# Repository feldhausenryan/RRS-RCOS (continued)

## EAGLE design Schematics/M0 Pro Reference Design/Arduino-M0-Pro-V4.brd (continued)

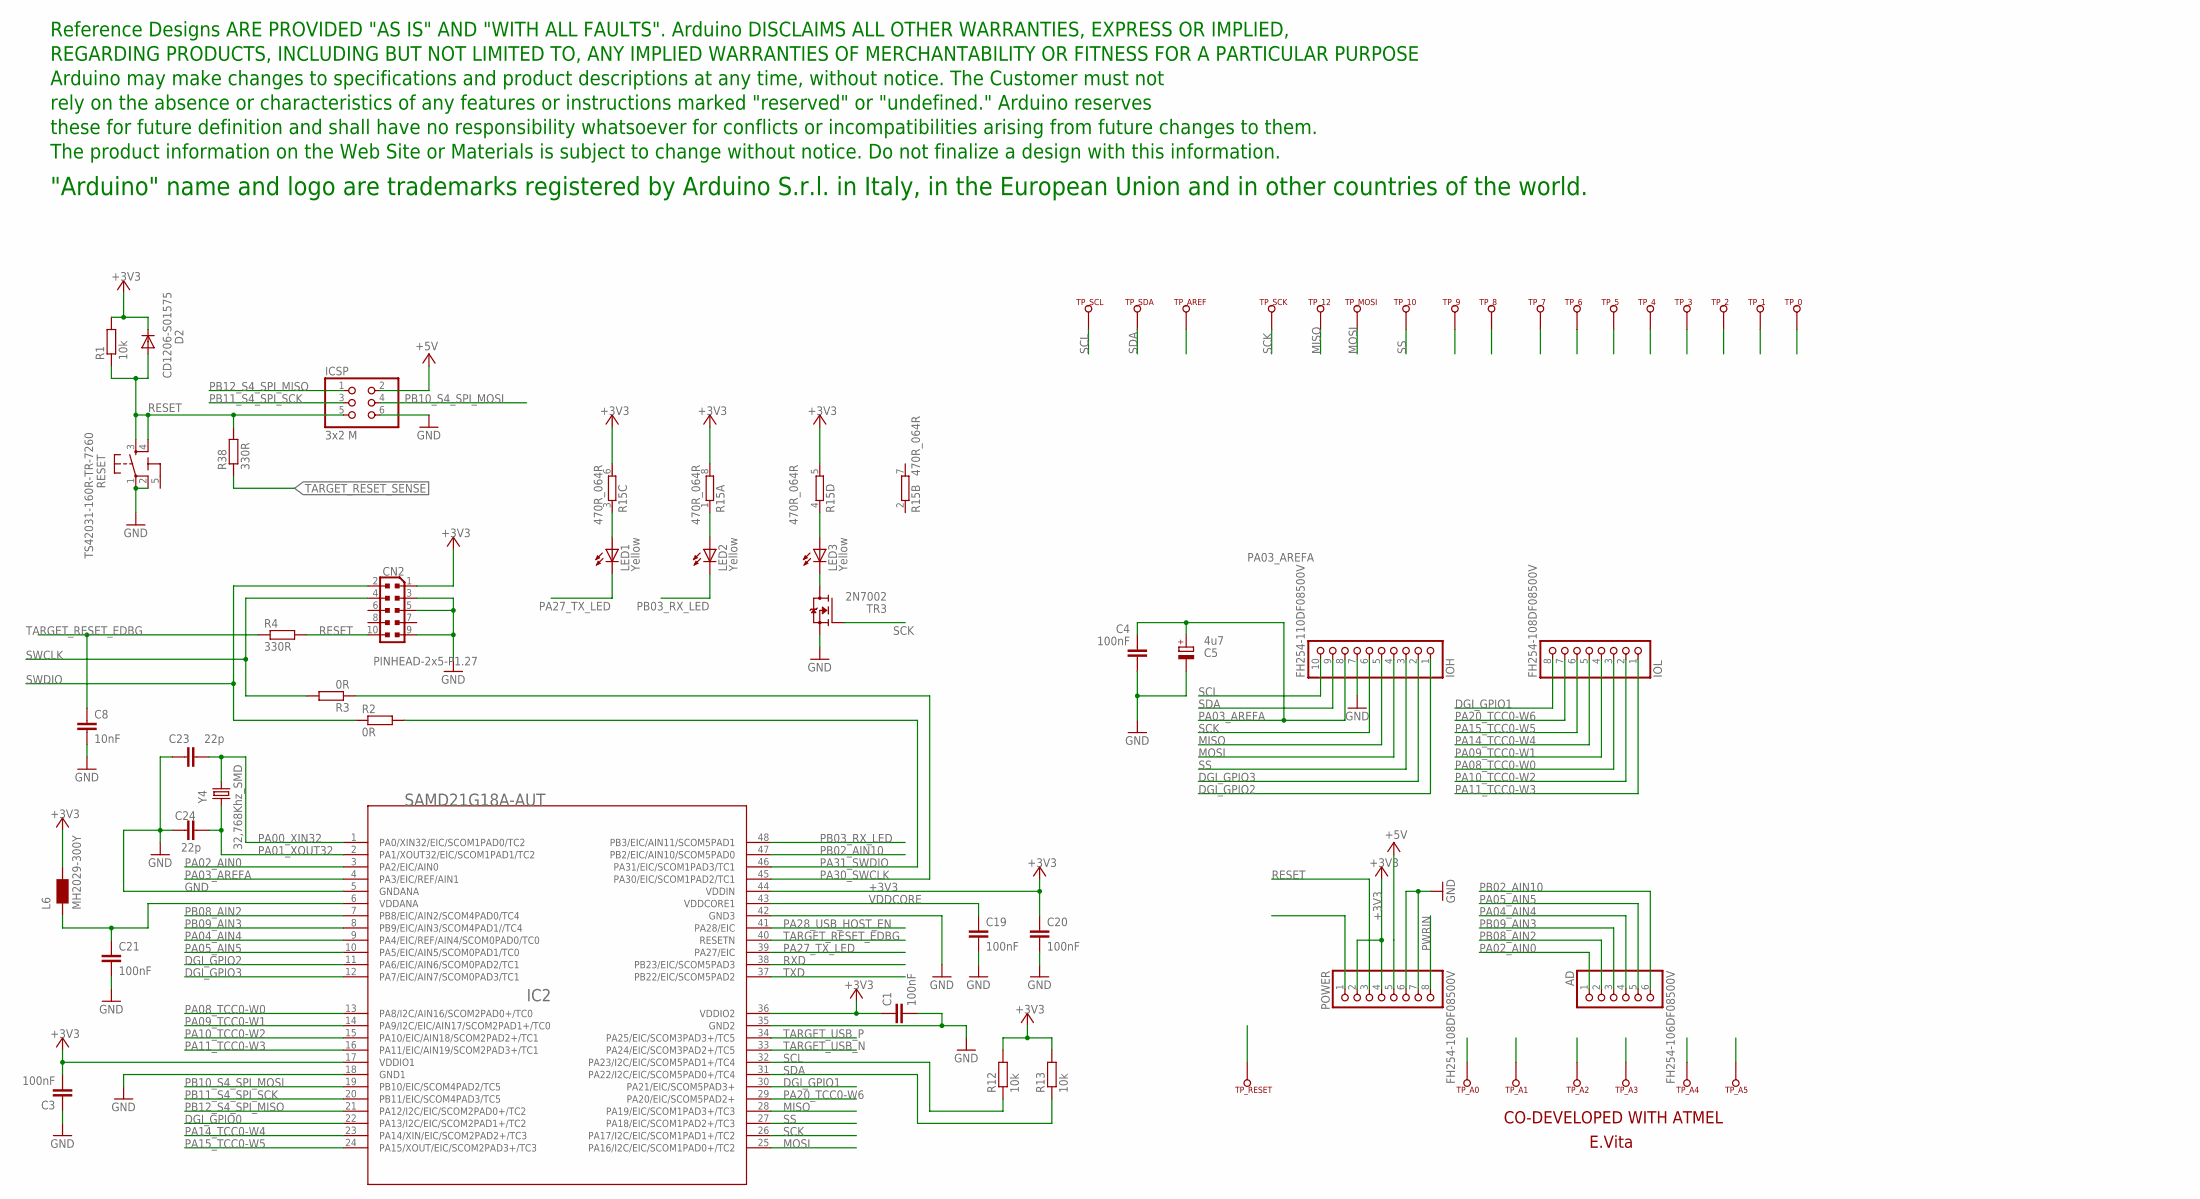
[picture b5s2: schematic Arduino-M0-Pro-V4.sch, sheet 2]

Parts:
AD: FH254-106DF08500V; 1X06
C1, C3, C4, C19, C20, C21: 100nF; C0603-ROUND
C5: 4u7; SMC_A
C8: 10nF; C0603-ROUND
C23, C24: 22p; C0603-ROUND
CN2: PINHEAD-2x5-P1.27; PINHEAD_2X05_127
D2: CD1206-S01575; MINIMELF
IC2: SAMD21G18A-AUT; TQFP48-7X7
ICSP: 3x2 M; 2X03
IOH: FH254-110DF08500V; 1X10
IOL: FH254-108DF08500V; 1X08
L6: MH2029-300Y; 0805
LED1, LED2, LED3: Yellow; CHIPLED_0805
POWER: FH254-108DF08500V; 1X08
R1, R12, R13: 10k; R0603-ROUND
R2, R3: 0R; R0603-ROUND
R4, R38: 330R; R0603-ROUND
R15: 470R_064R; CAY16
RESET: TS42031-160R-TR-7260; TS42
TP_0, TP_1, TP_2, TP_3, TP_4, TP_5, TP_6, TP_7, TP_8, TP_9, TP_10, TP_12: TP_SP; TP-SP
TP_A0, TP_A1, TP_A2, TP_A3, TP_A4, TP_A5: TP_SP; TP-SP
TP_AREF: TP_SP; TP-SP
TP_MOSI: TP_SP; TP-SP
TP_RESET: TP_SP; TP-SP
TP_SCK: TP_SP; TP-SP
TP_SCL: TP_SP; TP-SP
TP_SDA: TP_SP; TP-SP
TR3: 2N7002; SOT-23
U$2: DISCLAIMER
Y4: 32,768Khz_SMD; RESONATOR_EPSON_FC_145

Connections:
5-GND: RESET.5 (5-GND)
+3V3: C1.1, C3.2, C20.1, CN2.1, D2.C, IC2.17 (VDDIO1), IC2.36 (VDDIO2), IC2.44 (VDDIN), L6.2, POWER.2, POWER.4, R1.2, R12.2, R13.2, R15.5 (2), R15.6 (2), R15.8 (2); also elsewhere on the board
+5V: ICSP.2, POWER.5; also elsewhere on the board
DGI_GPIO0: IC2.22 (PA13/I2C/EIC/SCOM2PAD1+/TC2); also elsewhere on the board
DGI_GPIO1: IC2.30 (PA21/EIC/SCOM5PAD3+), IOL.8, TP_7.X; also elsewhere on the board
DGI_GPIO2: IC2.11 (PA6/EIC/AIN6/SCOM0PAD2/TC1), IOH.1, TP_8.X; also elsewhere on the board
DGI_GPIO3: IC2.12 (PA7/EIC/AIN7/SCOM0PAD3/TC1), IOH.2, TP_9.X; also elsewhere on the board
GND: C1.2, C3.1, C4.2, C5.-, C8.2, C19.2, C20.2, C21.2, C23.1, C24.1, CN2.3, CN2.5, CN2.9, IC2.5 (GNDANA), IC2.18 (GND1), IC2.35 (GND2), IC2.42 (GND3), ICSP.6, IOH.7, POWER.6, POWER.7, RESET.1, RESET.2, TR3.2 (S); also elsewhere on the board
MISO: IC2.28 (PA19/EIC/SCOM1PAD3+/TC3), IOH.5, TP_12.X; also elsewhere on the board
MOSI: IC2.25 (PA16/I2C/EIC/SCOM1PAD0+/TC2), IOH.4, TP_MOSI.X; also elsewhere on the board
unnamed: LED3.C, TR3.1 (D)
unnamed: C21.1, IC2.6 (VDDANA), L6.1
unnamed: LED1.A, R15.3 (1)
unnamed: LED2.A, R15.1
unnamed: LED3.A, R15.4 (1)
PA00_XIN32: C23.2, IC2.1 (PA0/XIN32/EIC/SCOM1PAD0/TC2), Y4.P$2 (2)
PA01_XOUT32: C24.2, IC2.2 (PA1/XOUT32/EIC/SCOM1PAD1/TC2), Y4.P$1 (1)
PA02_AIN0: AD.1, IC2.3 (PA2/EIC/AIN0), TP_A0.X
PA03_AREFA: C4.1, C5.+, IC2.4 (PA3/EIC/REF/AIN1), IOH.8, TP_AREF.X
PA04_AIN4: AD.4, IC2.9 (PA4/EIC/REF/AIN4/SCOM0PAD0/TC0), TP_A3.X
PA05_AIN5: AD.5, IC2.10 (PA5/EIC/AIN5/SCOM0PAD1/TC0), TP_A4.X
PA08_TCC0-W0: IC2.13 (PA8/I2C/AIN16/SCOM2PAD0+/TC0), IOL.3, TP_2.X
PA09_TCC0-W1: IC2.14 (PA9/I2C/EIC/AIN17/SCOM2PAD1+/TC0), IOL.4, TP_3.X
PA10_TCC0-W2: IC2.15 (PA10/EIC/AIN18/SCOM2PAD2+/TC1), IOL.2, TP_1.X
PA11_TCC0-W3: IC2.16 (PA11/EIC/AIN19/SCOM2PAD3+/TC1), IOL.1, TP_0.X
PA14_TCC0-W4: IC2.23 (PA14/XIN/EIC/SCOM2PAD2+/TC3), IOL.5, TP_4.X
PA15_TCC0-W5: IC2.24 (PA15/XOUT/EIC/SCOM2PAD3+/TC3), IOL.6, TP_5.X
PA20_TCC0-W6: IC2.29 (PA20/EIC/SCOM5PAD2+), IOL.7, TP_6.X
PA27_TX_LED: IC2.39 (PA27/EIC), LED1.C
PA28_USB_HOST_EN: IC2.41 (PA28/EIC); also elsewhere on the board
PA30_SWCLK: IC2.45 (PA30/EIC/SCOM1PAD2/TC1), R3.1
PA31_SWDIO: IC2.46 (PA31/EIC/SCOM1PAD3/TC1), R2.2
PB02_AIN10: AD.6, IC2.47 (PB2/EIC/AIN10/SCOM5PAD0), TP_A5.X
PB03_RX_LED: IC2.48 (PB3/EIC/AIN11/SCOM5PAD1), LED2.C
PB08_AIN2: AD.2, IC2.7 (PB8/EIC/AIN2/SCOM4PAD0/TC4), TP_A1.X
PB09_AIN3: AD.3, IC2.8 (PB9/EIC/AIN3/SCOM4PAD1//TC4), TP_A2.X
PB10_S4_SPI_MOSI: IC2.19 (PB10/EIC/SCOM4PAD2/TC5), ICSP.4
PB11_S4_SPI_SCK: IC2.20 (PB11/EIC/SCOM4PAD3/TC5), ICSP.3
PB12_S4_SPI_MISO: IC2.21 (PA12/I2C/EIC/SCOM2PAD0+/TC2), ICSP.1
PWRIN: POWER.8; also elsewhere on the board
RESET: CN2.10, D2.A, ICSP.5, POWER.3, R1.1, R4.2, R38.2, RESET.3, RESET.4, TP_RESET.X
RXD: IC2.38 (PB23/EIC/SCOM5PAD3); also elsewhere on the board
SCK: IC2.26 (PA17/I2C/EIC/SCOM1PAD1+/TC2), IOH.6, TP_SCK.X, TR3.3 (G); also elsewhere on the board
SCL: IC2.32 (PA23/I2C/EIC/SCOM5PAD1+/TC4), IOH.10, R12.1, TP_SCL.X; also elsewhere on the board
SDA: IC2.31 (PA22/I2C/EIC/SCOM5PAD0+/TC4), IOH.9, R13.1, TP_SDA.X; also elsewhere on the board
SS: IC2.27 (PA18/EIC/SCOM1PAD2+/TC3), IOH.3, TP_10.X; also elsewhere on the board
SWCLK: CN2.4, R3.2; also elsewhere on the board
SWDIO: CN2.2, R2.1; also elsewhere on the board
TARGET_RESET_EDBG: C8.1, IC2.40 (RESETN), R4.1; also elsewhere on the board
TARGET_RESET_SENSE: R38.1; also elsewhere on the board
TARGET_USB_N: IC2.33 (PA24/EIC/SCOM3PAD2+/TC5); also elsewhere on the board
TARGET_USB_P: IC2.34 (PA25/EIC/SCOM3PAD3+/TC5); also elsewhere on the board
TXD: IC2.37 (PB22/EIC/SCOM5PAD2); also elsewhere on the board
VDDCORE: C19.1, IC2.43 (VDDCORE1)

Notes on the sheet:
CO-DEVELOPED WITH ATMEL
E.Vita

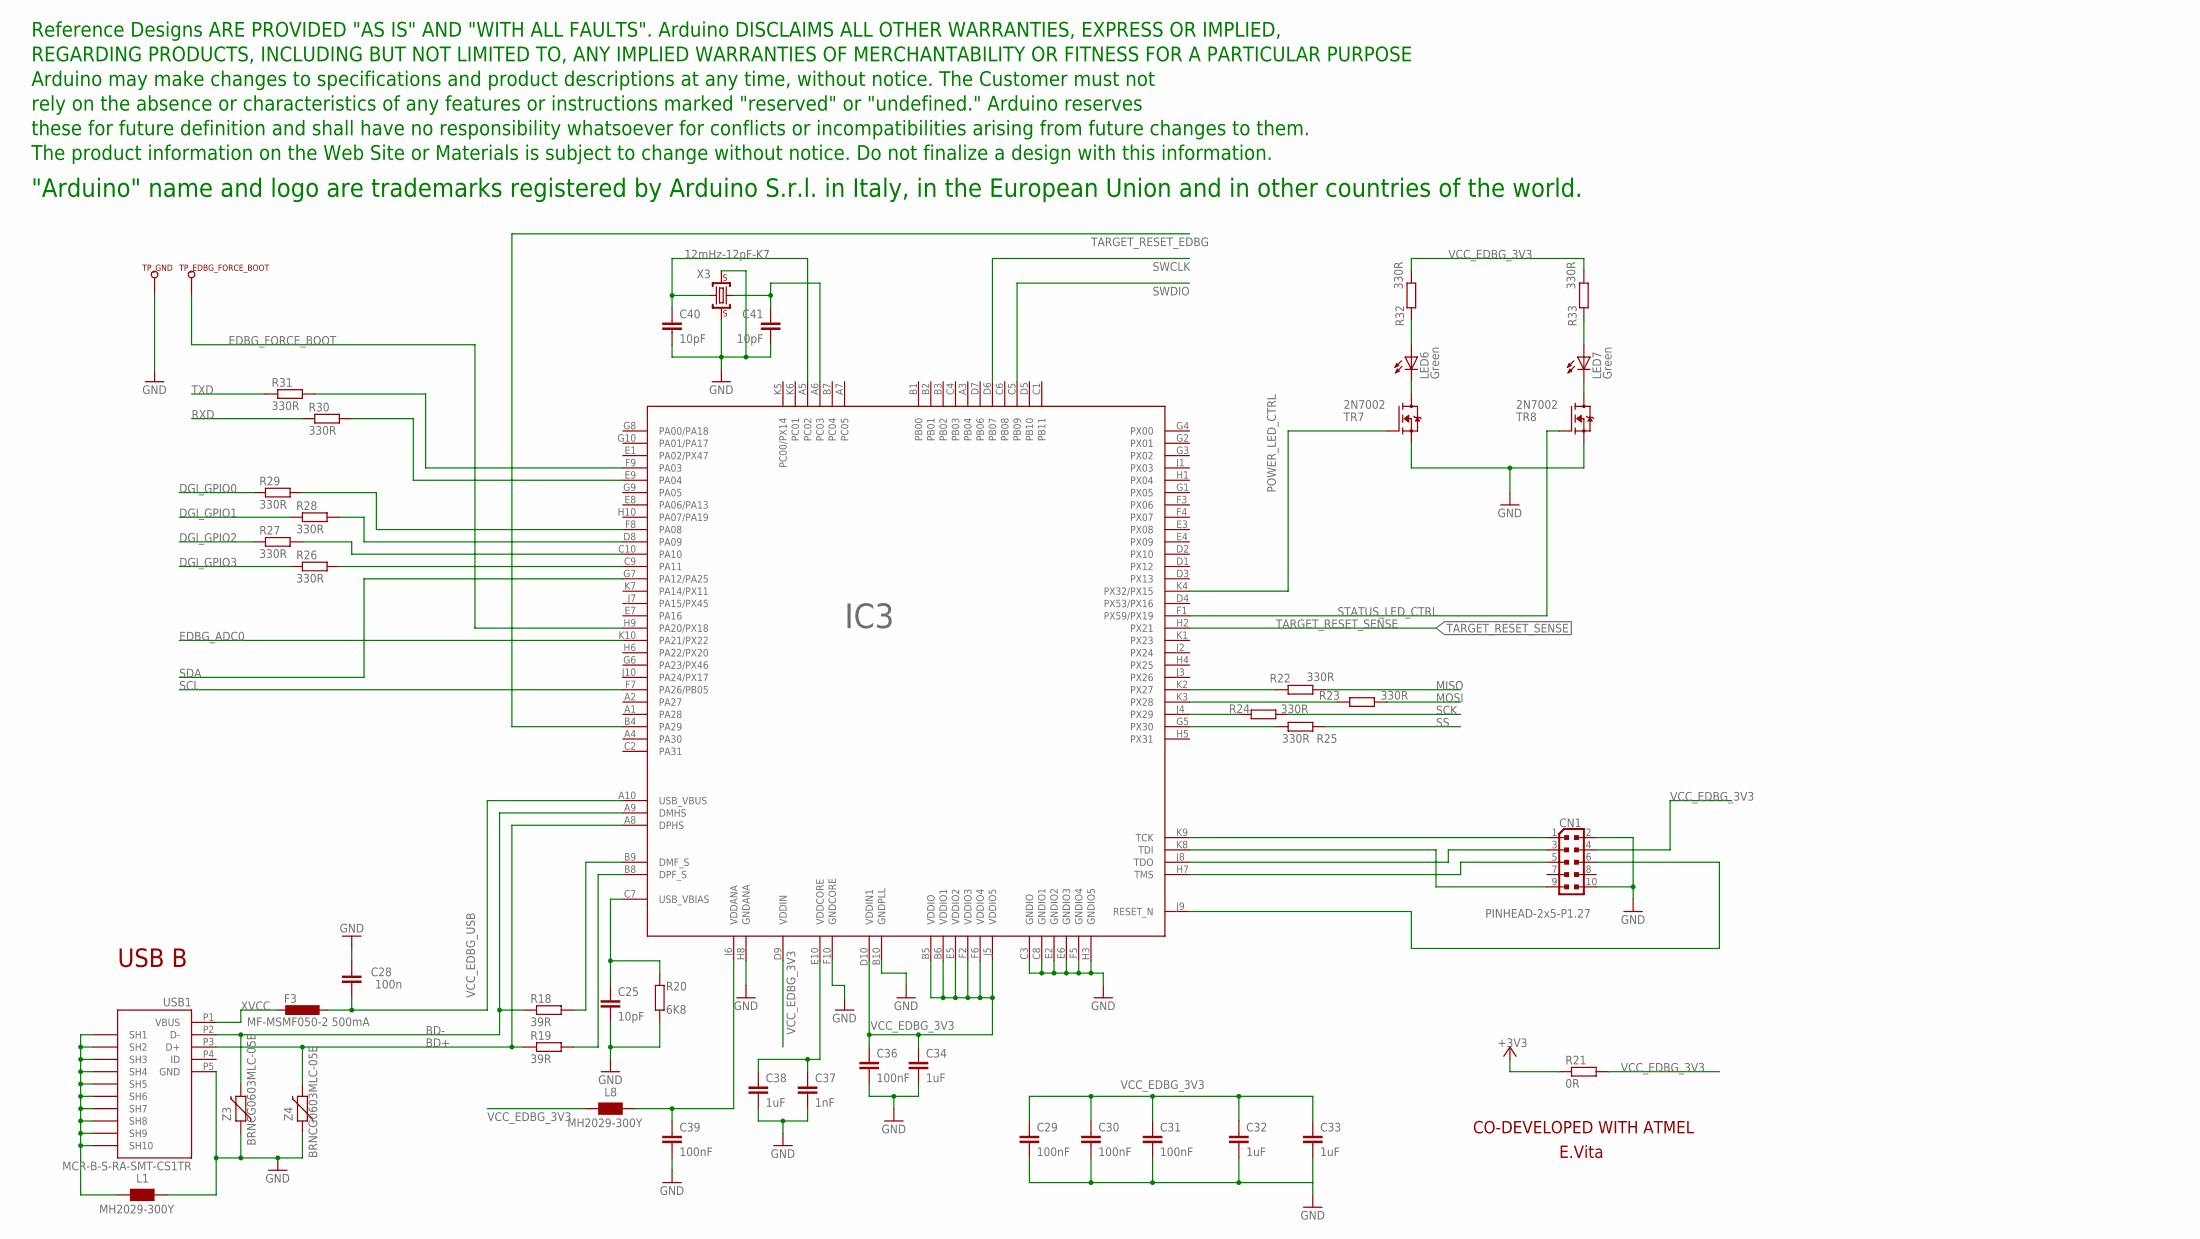
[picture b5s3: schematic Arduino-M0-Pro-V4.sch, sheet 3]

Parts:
C25, C40, C41: 10pF; C0603-ROUND
C28: 100n; C0603-ROUND
C29, C30, C31, C36, C39: 100nF; C0603-ROUND
C32, C33, C34, C38: 1uF; C0603-ROUND
C37: 1nF; C0603-ROUND
CN1: PINHEAD-2x5-P1.27; PINHEAD_2X05_127
F3: MF-MSMF050-2 500mA; L1812
IC3: 1791_AT32UC3A4256HHB-C1UR; VFBGA100
L1, L8: MH2029-300Y; 0805
LED6, LED7: Green; CHIPLED_0805
R18, R19: 39R; R0603-ROUND
R20: 6K8; R0603-ROUND
R21: 0R; R0603-ROUND
R22, R23, R24, R25, R26, R27, R28, R29, R30, R31, R32, R33: 330R; R0603-ROUND
TP_EDBG_FORCE_BOOT: TP_SP; TP-SP
TP_GND: TP_SP; TP-SP
TR7, TR8: 2N7002; SOT-23
U$3: DISCLAIMER
USB1: MCR-B-S-RA-SMT-CS1TR; CON2_USB_MICRO_B_AT
X3: 12mHz-12pF-K7; CRYSTAL-3.2-2.5
Z3, Z4: BRNCG0603MLC-05E; CT/CN0603

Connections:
+3V3: R21.1; also elsewhere on the board
BD+: IC3.A8 (DPHS), R19.1, USB1.P3 (D+), Z4.2
BD-: IC3.A9 (DMHS), R18.1, USB1.P2 (D-), Z3.2
DGI_GPIO0: R29.1; also elsewhere on the board
DGI_GPIO1: R28.1; also elsewhere on the board
DGI_GPIO2: R27.1; also elsewhere on the board
DGI_GPIO3: R26.1; also elsewhere on the board
EDBG_ADC0: IC3.K10 (PA21/PX22); also elsewhere on the board
EDBG_FORCE_BOOT: IC3.H9 (PA20/PX18), TP_EDBG_FORCE_BOOT.X
GND: C25.2, C28.2, C29.2, C30.2, C31.2, C32.2, C33.2, C34.2, C36.2, C37.2, C38.2, C39.2, C40.2, C41.2, CN1.2, CN1.10, IC3.B10 (GNDPLL), IC3.C3 (GNDIO), IC3.C8 (GNDIO1), IC3.E2 (GNDIO2), IC3.E6 (GNDIO3), IC3.F5 (GNDIO4), IC3.F10 (GNDCORE), IC3.H3 (GNDIO5), IC3.H8 (GNDANA), L1.2, R20.1, TP_GND.X, TR7.2 (S), TR8.2 (S), USB1.P5 (GND), X3.2 (GND), X3.4 (GND), Z3.1, Z4.1; also elsewhere on the board
MISO: R22.2; also elsewhere on the board
MOSI: R23.2; also elsewhere on the board
unnamed: LED6.C, TR7.1 (D)
unnamed: LED7.C, TR8.1 (D)
unnamed: L1.1, USB1.P$1 (SH7), USB1.P$2 (SH8), USB1.P$3 (SH9), USB1.P$4 (SH10), USB1.P$5 (SH7), USB1.P$6 (SH8), USB1.P$7 (SH9), USB1.P$8 (SH10), USB1.S1 (SH1), USB1.S2 (SH2), USB1.S3 (SH3), USB1.S4 (SH4), USB1.S5 (SH5), USB1.S6 (SH6)
unnamed: IC3.B9 (DMF_S), R18.2
unnamed: IC3.B8 (DPF_S), R19.2
unnamed: C25.1, IC3.C7 (USB_VBIAS), R20.2
unnamed: C41.1, IC3.A6 (PC03), X3.1 (C1)
unnamed: C40.1, IC3.A5 (PC02), X3.3 (C2)
unnamed: C37.1, C38.1, IC3.E10 (VDDCORE)
unnamed: C39.1, IC3.J6 (VDDANA), L8.2
unnamed: IC3.K2 (PX27), R22.1
unnamed: IC3.K3 (PX28), R23.1
unnamed: IC3.J4 (PX29), R24.1
unnamed: IC3.G5 (PX30), R25.1
unnamed: IC3.C9 (PA11), R26.2
unnamed: IC3.C10 (PA10), R27.2
unnamed: IC3.D8 (PA09), R28.2
unnamed: IC3.F8 (PA08), R29.2
unnamed: IC3.E9 (PA04), R30.2
unnamed: IC3.F9 (PA03), R31.2
unnamed: CN1.1, IC3.K9 (TCK)
unnamed: CN1.9, IC3.K8 (TDI)
unnamed: CN1.3, IC3.J8 (TDO)
unnamed: CN1.5, IC3.H7 (TMS)
unnamed: CN1.6, IC3.J9 (RESET_N)
unnamed: LED6.A, R32.1
unnamed: LED7.A, R33.1
POWER_LED_CTRL: IC3.K4 (PX32/PX15), TR7.3 (G)
RXD: R30.1; also elsewhere on the board
SCK: R24.2; also elsewhere on the board
SCL: IC3.F7 (PA26/PB05); also elsewhere on the board
SDA: IC3.G7 (PA12/PA25); also elsewhere on the board
SS: R25.2; also elsewhere on the board
STATUS_LED_CTRL: IC3.F1 (PX59/PX19), TR8.3 (G)
SWCLK: IC3.D6 (PB07); also elsewhere on the board
SWDIO: IC3.C5 (PB09); also elsewhere on the board
TARGET_RESET_EDBG: IC3.B4 (PA29); also elsewhere on the board
TARGET_RESET_SENSE: IC3.H2 (PX21); also elsewhere on the board
TXD: R31.1; also elsewhere on the board
VCC_EDBG_3V3: C29.1, C30.1, C31.1, C32.1, C33.1, C34.1, C36.1, CN1.4, IC3.B5 (VDDIO), IC3.B6 (VDDIO1), IC3.D9 (VDDIN), IC3.D10 (VDDIN1), IC3.E5 (VDDIO2), IC3.F2 (VDDIO3), IC3.F6 (VDDIO4), IC3.J5 (VDDIO5), L8.1, R21.2, R32.2, R33.2
VCC_EDBG_USB: C28.1, F3.1, IC3.A10 (USB_VBUS); also elsewhere on the board
XVCC: F3.2, USB1.P1 (VBUS)

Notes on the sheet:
USB B
CO-DEVELOPED WITH ATMEL
E.Vita

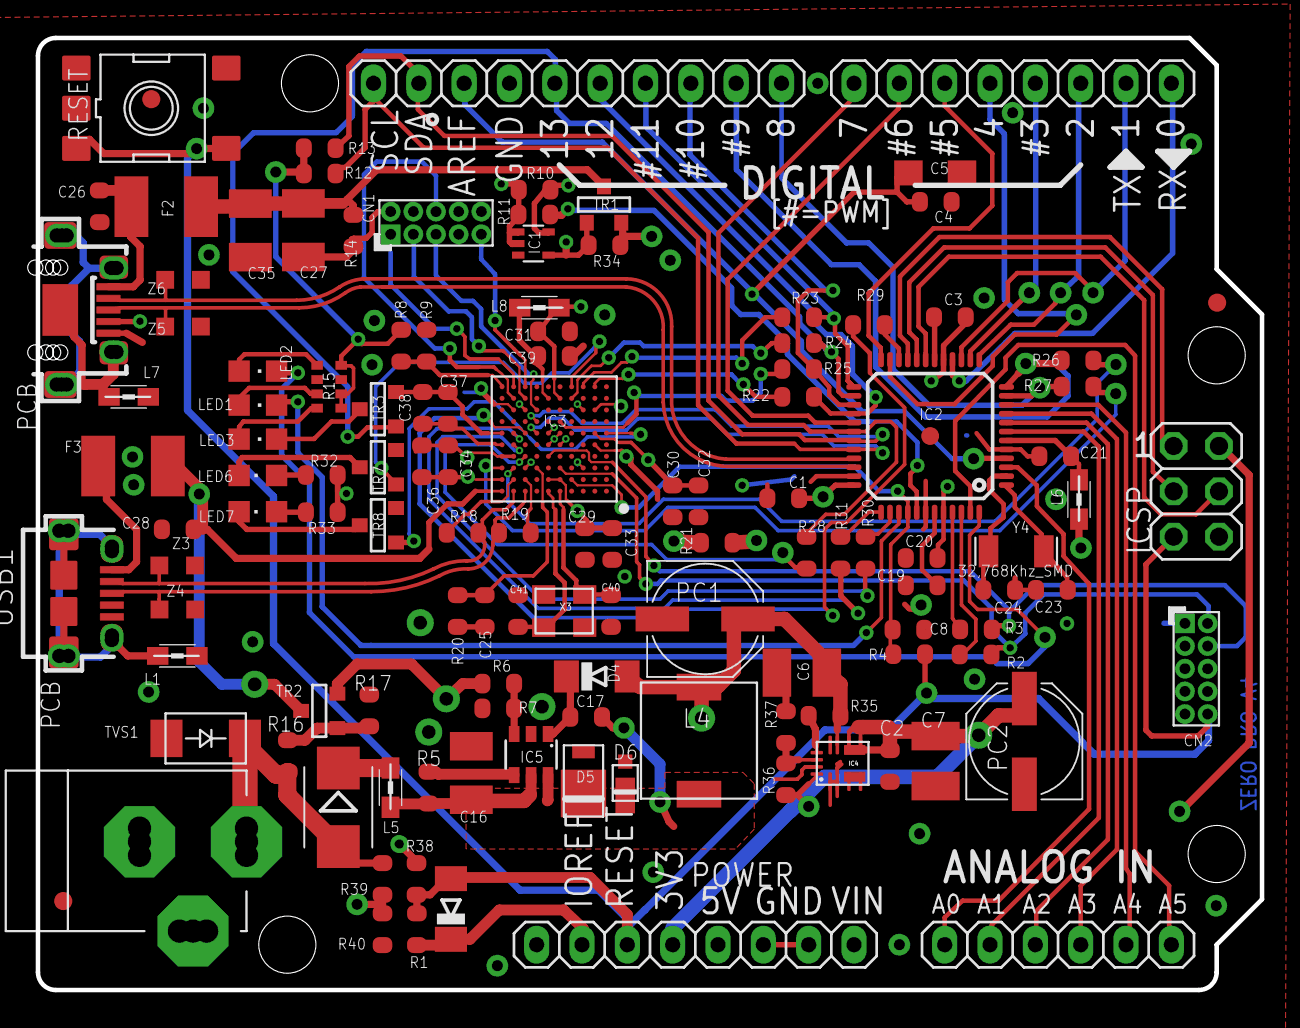
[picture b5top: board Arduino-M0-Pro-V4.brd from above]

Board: 4 copper layers, 68.6 x 53.3 mm, 156 parts (0 on the bottom side), 103 nets.

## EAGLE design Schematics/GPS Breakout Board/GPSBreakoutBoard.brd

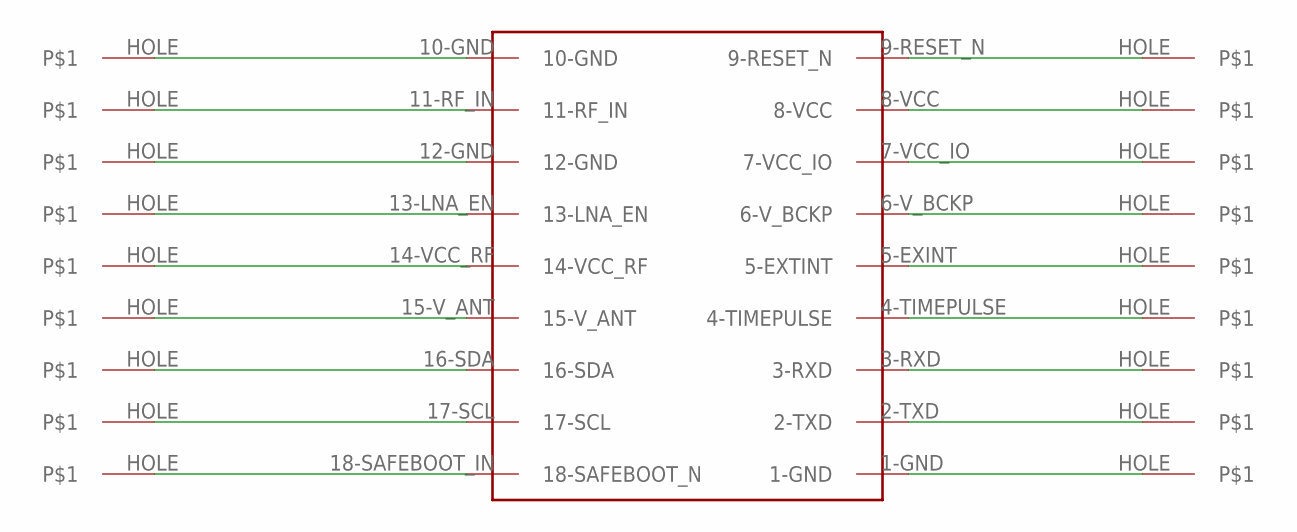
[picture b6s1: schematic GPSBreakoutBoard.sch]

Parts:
U$1: GPS_DEVICE; GPSMOUNT
U$2, U$3, U$4, U$5, U$6, U$7, U$8, U$9, U$10, U$11, U$12, U$13, U$14, U$15, U$16, U$17, U$18, U$19: HOLE; THING

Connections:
unnamed: U$1.10-GND, U$2.HOLE
unnamed: U$1.11-RF_IN, U$3.HOLE
unnamed: U$1.12-GND, U$4.HOLE
unnamed: U$1.13-LNA_EN, U$5.HOLE
unnamed: U$1.14-VCC_RF, U$6.HOLE
unnamed: U$1.15-V_ANT, U$7.HOLE
unnamed: U$1.16-SDA, U$8.HOLE
unnamed: U$1.17-SCL, U$9.HOLE
unnamed: U$1.18-SAFEBOOT_IN (18-SAFEBOOT_N), U$10.HOLE
unnamed: U$1.9-RESET_N, U$11.HOLE
unnamed: U$1.8-VCC, U$12.HOLE
unnamed: U$1.7-VCC_IO, U$13.HOLE
unnamed: U$1.6-V_BCKP, U$14.HOLE
unnamed: U$1.5-EXINT (5-EXTINT), U$15.HOLE
unnamed: U$1.4-TIMEPULSE, U$16.HOLE
unnamed: U$1.3-RXD, U$17.HOLE
unnamed: U$1.2-TXD, U$18.HOLE
unnamed: U$1.1-GND, U$19.HOLE

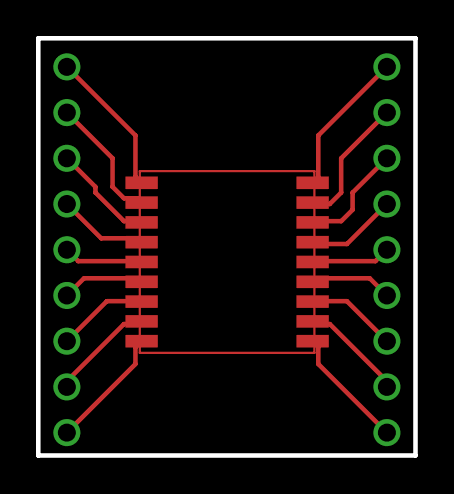
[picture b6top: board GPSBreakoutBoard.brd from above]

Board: 2 copper layers, 21.0 x 23.2 mm, 19 parts (0 on the bottom side), 18 nets.

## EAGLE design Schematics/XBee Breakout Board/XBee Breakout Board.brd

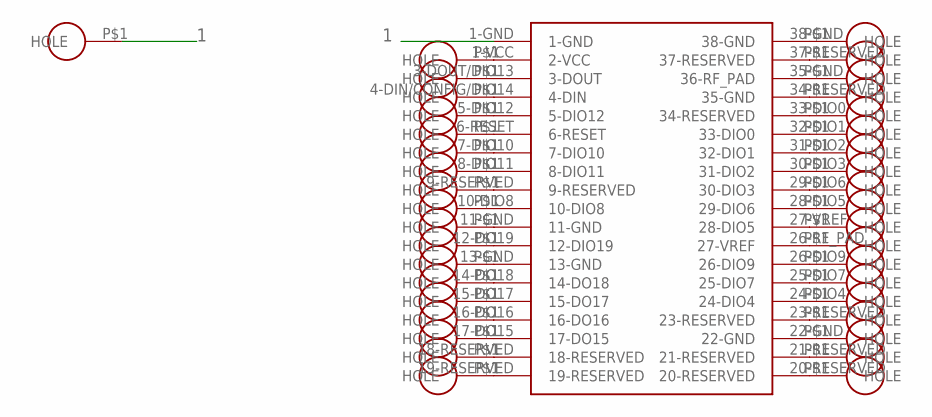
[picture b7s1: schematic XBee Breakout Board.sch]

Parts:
U$1: XBEE
U$2, U$3, U$4, U$5, U$6, U$7, U$8, U$9, U$10, U$11, U$12, U$13, U$14, U$15, U$16, U$17, U$18, U$19, U$20, U$21, U$22, U$23, U$24, U$25, U$26, U$27, U$28, U$29, U$30, U$31, U$32, U$33, U$34, U$35, U$36, U$37, U$38, U$39: HEADER-HOLE

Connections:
1: U$1.1-GND, U$2.P$1
unnamed: U$1.1-VCC (2-VCC), U$3.P$1
unnamed: U$1.3-DOUT/DIO13 (3-DOUT), U$4.P$1
unnamed: U$1.4-DIN/CONFIG/DIO14 (4-DIN), U$5.P$1
unnamed: U$1.5-DIO12, U$6.P$1
unnamed: U$1.6-RESET, U$7.P$1
unnamed: U$1.7-DIO10, U$8.P$1
unnamed: U$1.8-DIO11, U$9.P$1
unnamed: U$1.9-RESERVED, U$10.P$1
unnamed: U$1.10-DIO8, U$11.P$1
unnamed: U$1.11-GND, U$12.P$1
unnamed: U$1.12-DO19 (12-DIO19), U$13.P$1
unnamed: U$1.13-GND, U$14.P$1
unnamed: U$1.14-DO18, U$15.P$1
unnamed: U$1.15-DO17, U$16.P$1
unnamed: U$1.16-DO16, U$17.P$1
unnamed: U$1.17-DO15, U$18.P$1
unnamed: U$1.18-RESERVED, U$19.P$1
unnamed: U$1.19-RESERVED, U$20.P$1
unnamed: U$1.38-GND, U$21.P$1
unnamed: U$1.37-RESERVED, U$22.P$1
unnamed: U$1.35-GND (36-RF_PAD), U$23.P$1
unnamed: U$1.34-RESERVED (35-GND), U$24.P$1
unnamed: U$1.33-DIO0 (34-RESERVED), U$25.P$1
unnamed: U$1.32-DIO1 (33-DIO0), U$26.P$1
unnamed: U$1.31-DIO2 (32-DIO1), U$27.P$1
unnamed: U$1.30-DIO3 (31-DIO2), U$28.P$1
unnamed: U$1.29-DIO6 (30-DIO3), U$29.P$1
unnamed: U$1.28-DIO5 (29-DIO6), U$30.P$1
unnamed: U$1.27-VREF (28-DIO5), U$31.P$1
unnamed: U$1.26-RF_PAD (27-VREF), U$32.P$1
unnamed: U$1.26-DIO9, U$33.P$1
unnamed: U$1.25-DIO7, U$34.P$1
unnamed: U$1.23-RESERVED, U$35.P$1
unnamed: U$1.24-DIO4, U$36.P$1
unnamed: U$1.21-RESERVED, U$37.P$1
unnamed: U$1.22-GND, U$38.P$1
unnamed: U$1.20-RESERVED, U$39.P$1

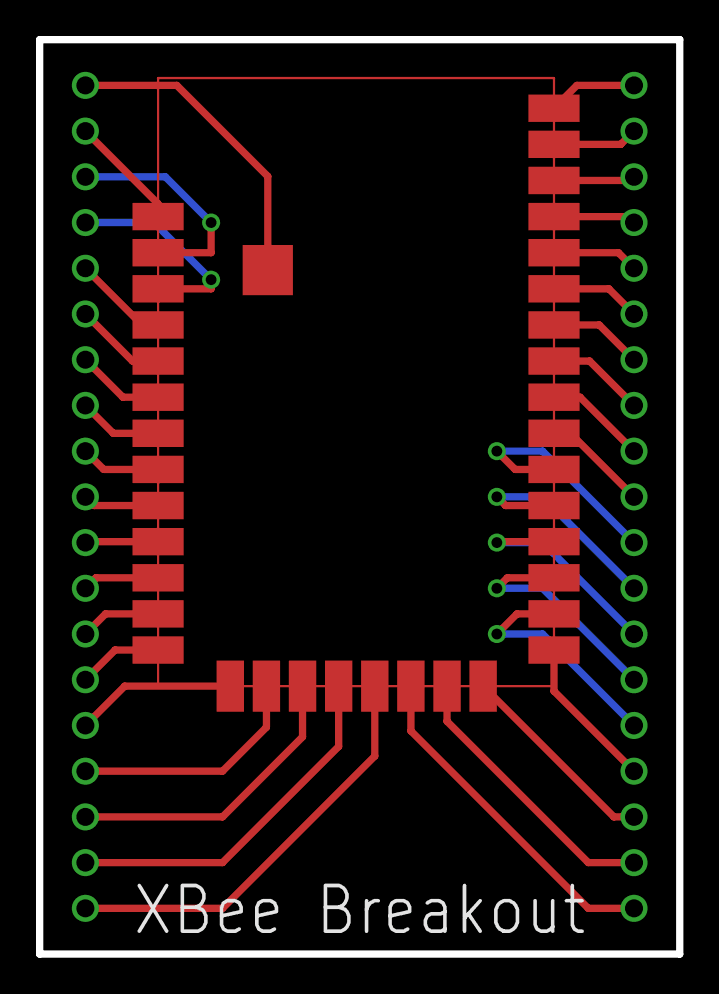
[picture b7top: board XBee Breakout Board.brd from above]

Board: 2 copper layers, 35.6 x 50.8 mm, 39 parts (0 on the bottom side), 38 nets.
